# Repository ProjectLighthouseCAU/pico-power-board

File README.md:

# Schematic, PCB Layout and BOM for the new Power-and-Distribution Board
This PCB is meant to be used with the Raspberry Pi Pico with Ethernet e.g. Wiznet W5100S-EVB-Pico or W5500-EVB-Pico or optionally WiFi with the Pi Pico W.

## EDA Software and Manufacturer
The Design was made with KiCAD, a free and open-source program for electronic design automation (EDA).
It was chosen because a proprietary solution would be both very costly (or only available as a student) and also not free. Furthermore, we don't need the features that a commercial solution like Altium offers.
The PCBs will be manufactured and assembled at JLCPCB, a large chinese PCB manufacturing company based in Shenzhen that offers cheap services, good quality, fast assembly and shipping and also has a lot of parts ready in their own storage or source them directly from LCSC (big component distributor in China).

## Purpose and features of the PCB
The PCB acts as a kind of motherboard for the Pi Pico (+ e.g. W5100S or W5500) which can be mounted on top using two rows of 20 pin header sockets.
Further, it has a barrel jack for a 12V power supply and a step down converter from 12V to 3.3V to power the Pico and lamp microcontrollers.
The board features six 20-pin IDC connectors where Lighthouse lamps can be connected via flat cables.  
The connectors (and cables) contain an SPI bus (MISO, MOSI, SCK, CS), 3.3V, Reset, 12V (on six wires) and GND (on 8 wires).  
Additional fearures are:
- polyfuses for each lamp with a detection (via voltage divider) if the fuse has tripped
- current measurement IC (TI INA219) with a shunt resistor to monitor power draw
- thermal sensor (TI TMP112A) to monitor temperature
- I2C and UART breakout pins for testing, adding devices and hacking stuff together
- signal termination resistors for SPI data lines and RESET to reduce ringing and over-/undershoot (series termination for SCK, MOSI, CS and RESET, thevenin termination for MOSI)

## Design Decisions

### Microcontroller
The Raspberry Pi Pico together with the Wiznet W5500 (or W5100S) provides a performant, reliable and cheap alternative to other ethernet capable microcontrollers.  
The previously used Atmel/Microchip ATTiny841 with the ENC28J60 was too unreliable and had insufficient performance and memory.
Ethernet capable STM32 chips would be a good alternative but those that feature Ethernet support are too expensive and also require a complete board design (instead of the now chosen "motherboard" solution).
Teensy boards have great performance but are way too expensive. Same holds for Raspberry Pis and other single board computers.  
In fact, after a lot of research we found many wireless capable microcontrollers (e.g. the official Pi Pico W and ESP32) because of the increasing popularity of the Internet of Things (IoT) but finding good and cheap Ethernet capable MCUs was difficult.  
Therefore we were glad that Wiznet released their Pi Pico based boards.
The C/C++ Pico SDK is well documented and easy to work with and the Wiznet library is also okay and features the Berkeley socket API and some examples.
Nevertheless, we decided to rewrite the firmware in Rust for the Pi Pico with the W5500.

### Motherboard instead of complete "bare" chip design
We chose to design a simple motherboard for the finished Pi Pico board because it was easier and faster to design with less possibilities for mistakes (at least on the MCU side).  
We simply added a DC-Jack, six IDC connectors and a step-down-converter together with some sensors, fuses and connected everything accordingly.

### Fuses
We need fuses for each lamp because if we have one 10A fuse for all lamps and one lamp has a short circuit, then up to 10A may flow through that one lamp which is too much and could cause a fire.  
We measured the maximum current that a lamp can draw which is about 1.6A and selected a 2A fuse. The selected fuse is a polyfuse (or resettable fuse) which automatically resets itself (conducts again) after the current returns to a normal < 2A.  
We wanted to monitor if a fuse has tripped, so we took the 12V after the fuse, added a voltage divider to 3V and hooked that back up to the Pi Pico and also the reset line to that lamp.  
Therefore the lamp automatically resets (because reset is active low) and we don't need extra GPIOs on the Pico. If the Pico wants to manually reset a lamp, it just has to change the pin to output and pull it low. The current that then flows through the voltage divider and the GPIO is low enough for the maximum rating of the GPIO.

### Signal termination resistors

After looking at the SPI signal with an oscilloscope, we found out that the fast switching of voltage levels causes reflections on the end of the longer cables. These reflections interfere with each other constructively and cause ringing (voltage swings around the desired voltage at a rising/falling edge) and therefore over-/undershoot (voltage goes above/below the GPIO pins rated maximum/minimum voltage).  
While the SPI communication works and nothing broke yet, this over-/undervoltage could damage the GPIO pins or the whole microcontroller (both RP2040 and ATtiny841) in the long run.  
To fix this issue, we need to terminate the transmission line (cable) with properly sized terminating resistors with a suitable termination technique.  
Because we only change the hardware on one side of the transmission line, we need to choose the termination technique accordingly.  
There are three suitable termination techniques:
- Series termination (series resistor at the transmitter)
- Parallel termination (parallel resistor at the receiver, pull down to GND)
- Thevenin termination (voltage divider at the receiver)

#### Series termination for outgoing data lines
For the transmitting data lines (SCK, MOSI, CS, RESET), we chose series termination since it is the only termination that is recommended at the source. It also is the most widely used technique, gives good results and has no extra power usage. The only downside is that the resistor limits the current and therefore increases the rise-/fall-times of the signal (which is negligable in our case).

#### Thevenin termination for incoming data line
For the one incoming data line (MISO) we tried to use parallel termination but this technique has the downside that it draws a lot of current from the transmitter (ATtiny841) which it cannot provide. So the signal couldn't reach the required voltage for a logic 1.  
Alternatively we chose Thevenin termination, which uses a voltage divider at the receiving end to pull the line to a voltage between Vcc and GND. This makes it "easier" for the driver to pull the line high and low and solved the insufficient voltage issue. We chose to use resistors of equal size to pull the signal exaclty at the half of Vcc.

#### Terminating resistor value
The value for the terminating resistors was determined experimentally.
Ideally one would consult the datasheet of the cable for its characteristic impedance, but unfortunately no information about the installed cables was found.
So, we tried out several different resistor values and measured the maximum and minimum voltage, rise and fall time and visually inspected the ringing with an oscilloscope.
The results showed that a 100 Ohm resistor is suitable for series termination and two 200 Ohm resistors for Thevenin termination (since they are considered to be in parallel from the signals perspective, the combined resistance is 100 Ohm).
So the cables characteristic impedance is somewhere around 100 Ohm (+/- measurement inaccuracies and + ouput driver impedance).

#### Problem: SPI over long distance unshielded cable
We are aware that transmitting SPI signals over long unshielded cables can and will cause interference problems.  
The old system was designed like this to save on cost.
Adding transceivers for some kind of differential transmission on both ends and using shielded cables would be the ideal solution.  
But designing, buying and installing new transceiver boards for the lamps, new cables and connectors would be very time consuming and expensive.  
Since the old system worked well enough, we decided to try out a lower frequency, a line driver IC (which we found out was not needed), signal termination resistors and add some error detection (checksum/CRC).
Unfortunately, the return channel (MISO / lamp -> controller) had the most problems especially with longer transmissions of 8 bytes. This is partly caused by the unbuffered SPI data register of the ATtiny841. When the lamp doesn't update the data register in time, the controller reads (part of) the previous value. The only solution to fix this (after all optimizations) is to reduce the frequency.  

### Step-Down-Converter
We decided to use a drop-in replacement for a linear regulator since it provides a finished and tested solution for efficient voltage regulation and we don't need to calculate inductances and capacitances.
After all we are computer scientists and not electrical engineers and therefore will probably make mistakes.

Note that the original Pi Pico has a Step-Up/Step-Down converter builtin (with a maximum input of about 5V).
But the Wiznet W5100S-EVB-Pico has a linear regulator.
Because two Step-Downs can cause interference and a linear regulator is not well suited for "converting" 3.3V to 3.3V (it needs at least 1V higher input voltage), we opted to power the Pico using the 3V3(OUT)-pin instead of the VSYS-pin which connects to the point after its internal linear regulator.

### DC-Barrel-Jack
The barrel jack should support our 12V power supply connectors and be rated for 10A. It should also have an inner pin diameter of 2.5mm and an outer barrel diameter of 5.5mm (the outer diameter can be larger if it has a spring mechanism that holds the plug).

### Debug and extension header
We added a 6-pin header as a breakout for some GPIOs of the pico.
They can be used for debugging or manually extending some functionality.  
These are:  
- UART (TX+RX)
- I2C (SDA+SCL)
- 3.3V
- GND

### Mounting Holes
The mounting holes are spaced to fit our old plastic cases.
(84mmx55.5mm)

### Current Measurement
We chose the INA219 from Texas Instruments together with a 10mOhm current shunt resistor. The INA219 features a current sensing amplifier, a precision ADC and an I2C interface.
We can configure the chip with the shunt resistance and then query voltage-drop, input-voltage, current and power.

### Temperature Measurement
The Pico has a builtin temperature sensor but it is not very accurate and also inside of the chip where any heat from the CPU is measured as well. We therefore added a small temperature sensor from Texas Instruments (TMP112A) which also has an I2C interface. This temperature sensor is installed near the barrel jack to measure the temperature increase from the current flowing through the 12V trace.

### Bypass capacitors
The step-down-converter has a 100nF and a 10uF capacitor on the 12V side and a 22uF capacitor on the 3.3V side (all ceramic as mentioned in the datasheet).
The temperature sensor has a 10nF and the current sensor has a 100nF capacitor (as mentioned in the datasheet).
The header for the Pi Pico has a 100nF and a 22pF capacitor at the 3.3V input.

## Insecurities / TODOs / To-Checks

### Trace width
Especially 12V high current traces (to the lamps).

### Trace spacing and routing
- enough spacing between tracks?
- too many vias?
- signal trace routing okay?

### Current return paths through GND plane
Is the current return path through the GND plane large and direct enough?
The signal traces on the bottom side were routed back to the top for short distances to keep a clear path from the GND of the connectors to the GND of the barrel jack.

### Double-check components
- check datasheets, bypass capacitors
- check footprints
- check placement and rotation files
- check BOM

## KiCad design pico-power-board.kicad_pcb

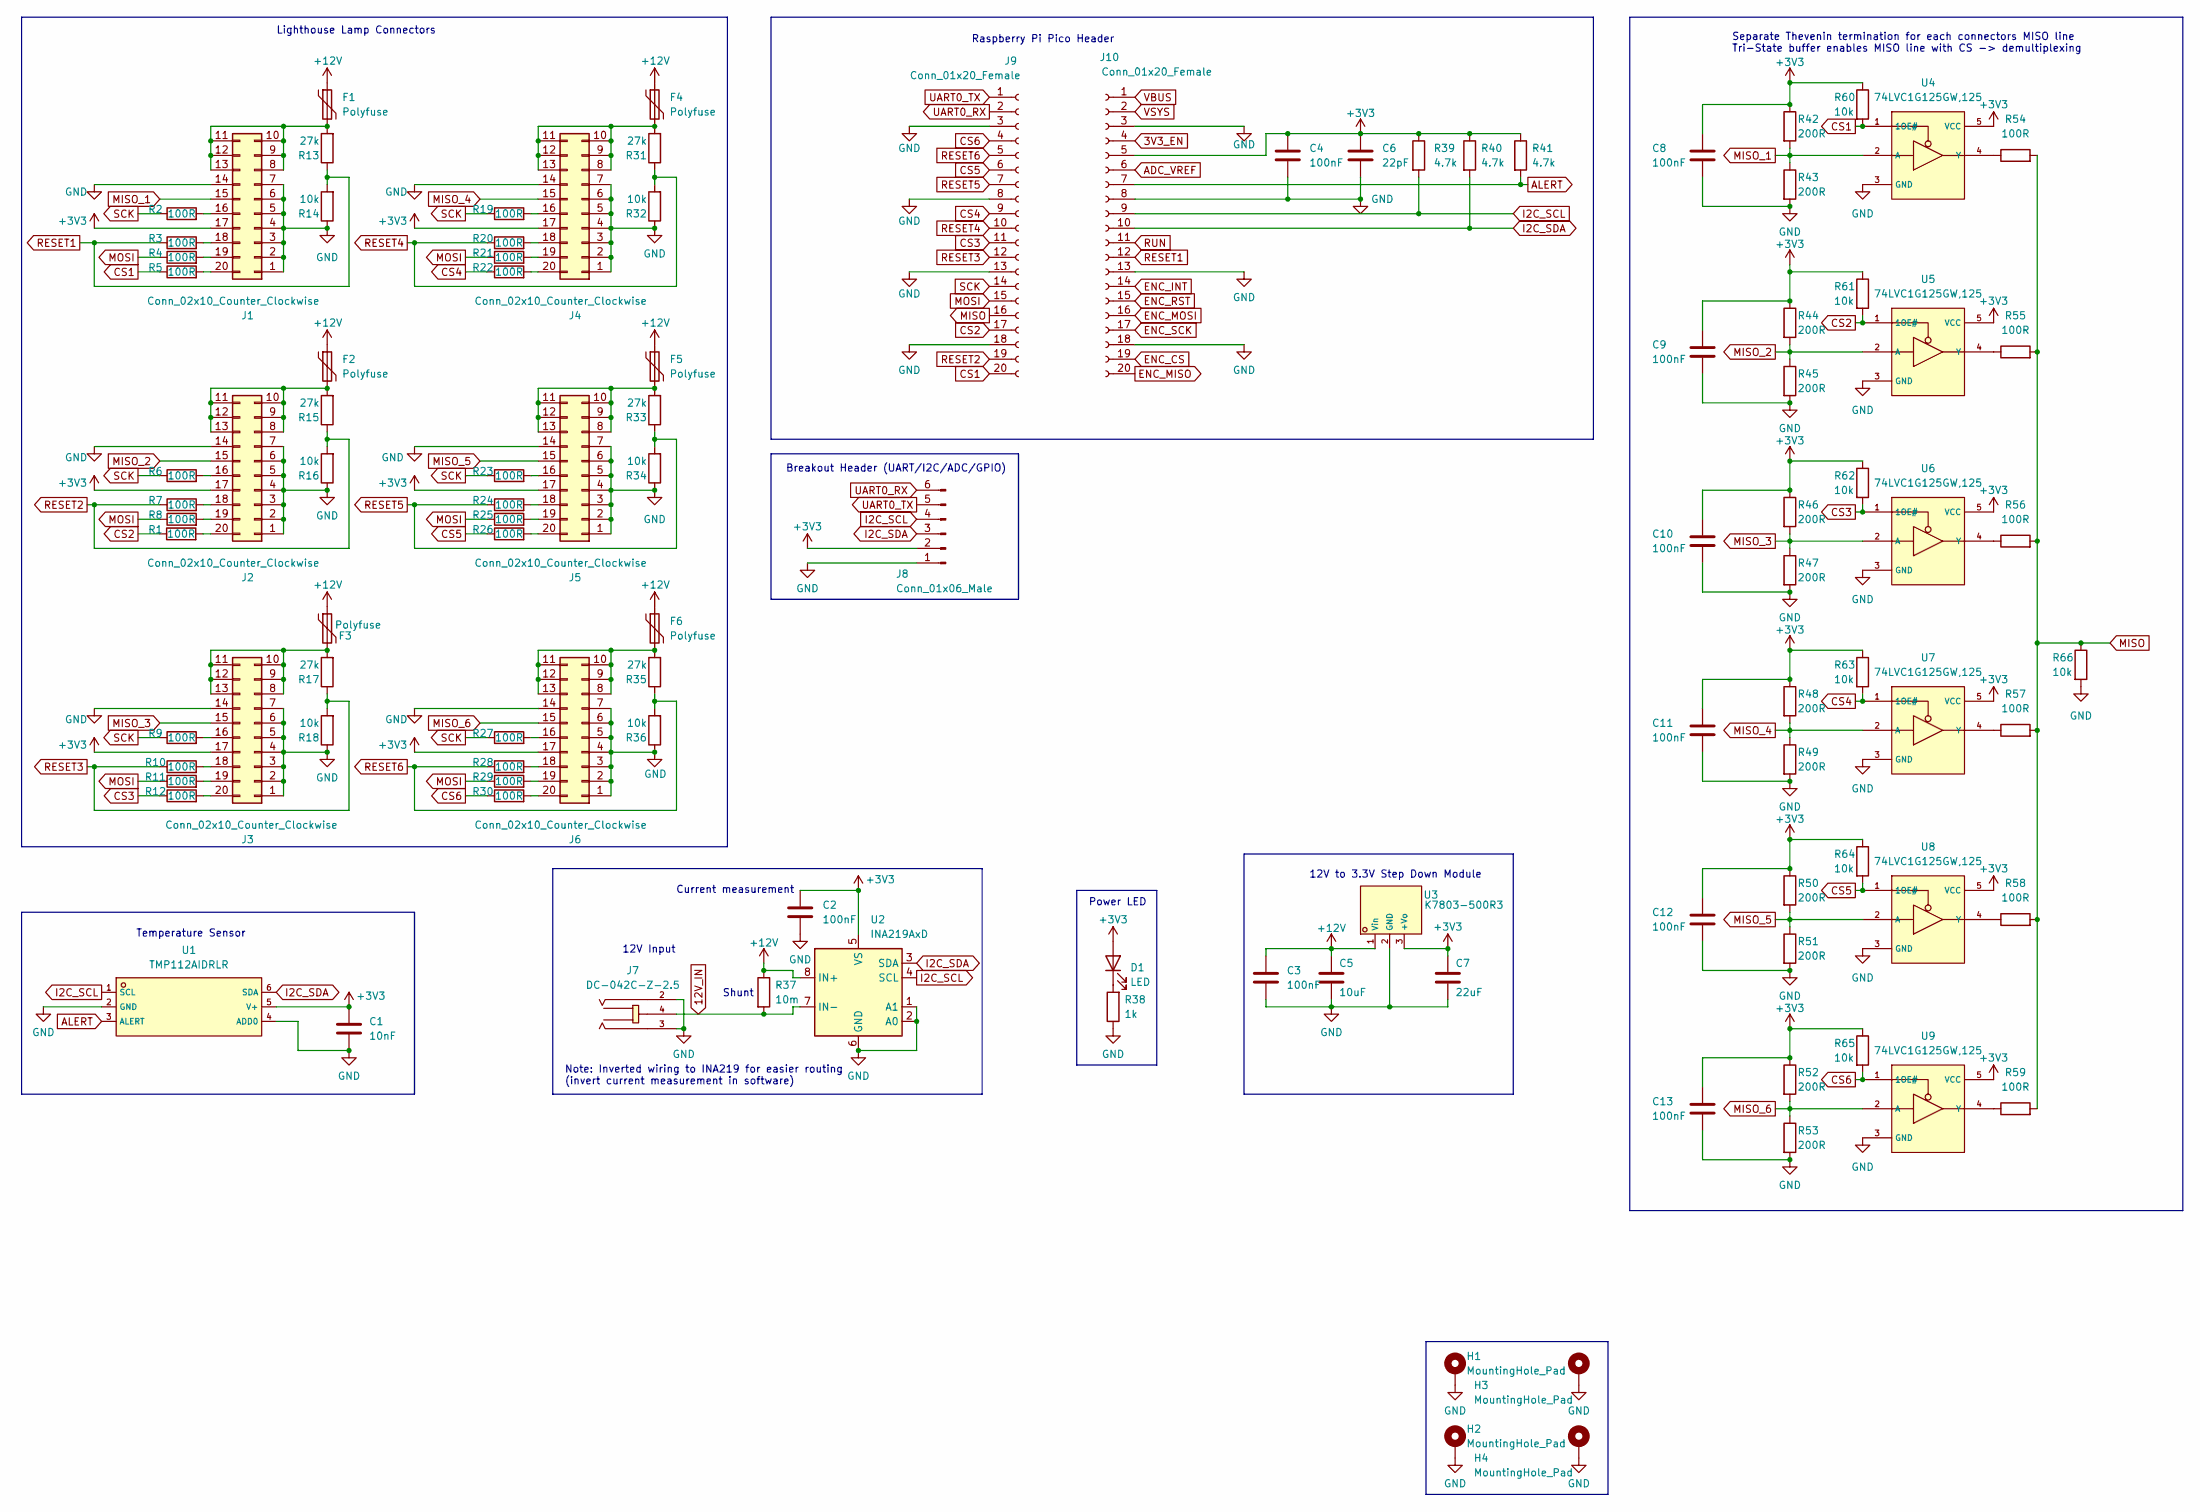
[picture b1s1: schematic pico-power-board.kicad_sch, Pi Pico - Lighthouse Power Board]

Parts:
C1: 10nF; C_0603_1608Metric; JLC 0603
C2, C3, C4, C8, C9, C10, C11, C12, C13: 100nF; C_0603_1608Metric; JLC 0603
C5: 10uF; C_1206_3216Metric; JLC 1206
C6: 22pF; C_0603_1608Metric; JLC 0603
C7: 22uF; C_0805_2012Metric; JLC 0805
D1: LED; LED_0603_1608Metric; JLC 0603
F1, F2, F3, F4, F5, F6: Polyfuse; Fuse_1206_3216Metric; JLC 1206
H1, H2, H3, H4: MountingHole_Pad; MountingHole_3.2mm_M3_DIN965_Pad
J1, J2, J3, J4, J5, J6: Conn_02x10_Counter_Clockwise; IDC-Header_2x10_P2.54mm_Vertical; JLC Plugin,P=2.54mm
J7: DC-042C-Z-2.5; DC-IN-TH_DC-042C-Z-2.5; LCSC C2880557
J8: Conn_01x06_Male; PinHeader_1x06_P2.54mm_Vertical; JLC Plugin,P=2.54mm
J9, J10: Conn_01x20_Female; PinSocket_1x20_P2.54mm_Vertical; JLC Plugin,P=2.54mm
R1, R2, R3, R4, R5, R6, R7, R8, R9, R10, R11, R12, R19, R20, R21, R22, R23, R24, R25, R26, R27, R28, R29, R30, R54, R55, R56, R57, R58, R59: 100R; R_0603_1608Metric; JLC 0603
R13, R15, R17, R31, R33, R35: 27k; R_0603_1608Metric; LCSC C308131
R14, R16, R18, R32, R34, R36: 10k; R_0603_1608Metric; LCSC C25804
R37: 10m; R_1206_3216Metric; JLC 1206
R38: 1k; R_0603_1608Metric; JLC 0603
R39, R40, R41: 4.7k; R_0603_1608Metric; JLC 0603
R42, R43, R44, R45, R46, R47, R48, R49, R50, R51, R52, R53: 200R; R_0603_1608Metric; JLC 0603
R60, R61, R62, R63, R64, R65, R66: 10k; R_0603_1608Metric; JLC 0603
U1: TMP112AIDRLR; SOT-563_L1.6-W1.2-P0.50-LS1.6-BR; LCSC C28927
U2: INA219AxD; SOIC-8_3.9x4.9mm_P1.27mm; JLC SOIC-8_150mil
U3: K7803-500R3; PWRM-TH_K7803-500R3; LCSC C86736
U4, U5, U6, U7, U8, U9: 74LVC1G125GW,125; SOT-353_L2.1-W1.3-P0.65-LS2.3-BR; LCSC C12519

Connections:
3V3_EN: J10.4
12V_IN: J7.4, R37.2, U2.7 (IN-)
+3V3: C1.1, C2.2, C4.1, C6.1, C7.1, C8.1, C9.1, C10.1, C11.1, C12.1, C13.1, D1.2 (A), J1.17, J2.17, J3.17, J4.17, J5.17, J6.17, J8.2, J10.5, R39.1, R40.1, R41.1, R42.1, R44.1, R46.1, R48.1, R50.1, R52.1, R60.1, R61.1, R62.1, R63.1, R64.1, R65.1, U1.5 (V+), U2.5 (VS), U3.3 (+Vo), U4.5 (VCC), U5.5 (VCC), U6.5 (VCC), U7.5 (VCC), U8.5 (VCC), U9.5 (VCC)
+12V: C3.1, C5.1, F1.1, F2.1, F3.1, F4.1, F5.1, F6.1, R37.1, U2.8 (IN+), U3.1 (Vin)
ADC_VREF: J10.6
ALERT: J10.7, R41.2, U1.3 (ALERT)
CS1: J9.20, R5.1, R60.2, U4.1 (1OE#)
CS2: J9.17, R1.1, R61.2, U5.1 (1OE#)
CS3: J9.11, R12.1, R62.2, U6.1 (1OE#)
CS4: J9.9, R22.1, R63.2, U7.1 (1OE#)
CS5: J9.6, R26.1, R64.2, U8.1 (1OE#)
CS6: J9.4, R30.1, R65.2, U9.1 (1OE#)
ENC_CS: J10.19
ENC_INT: J10.14
ENC_MISO: J10.20
ENC_MOSI: J10.16
ENC_RST: J10.15
ENC_SCK: J10.17
GND: C1.2, C2.1, C3.2, C4.2, C5.2, C6.2, C7.2, C8.2, C9.2, C10.2, C11.2, C12.2, C13.2, H1.1, H2.1, H3.1, H4.1, J1.1, J1.2, J1.3, J1.4, J1.5, J1.6, J1.7, J1.14, J2.1, J2.2, J2.3, J2.4, J2.5, J2.6, J2.7, J2.14, J3.1, J3.2, J3.3, J3.4, J3.5, J3.6, J3.7, J3.14, J4.1, J4.2, J4.3, J4.4, J4.5, J4.6, J4.7, J4.14, J5.1, J5.2, J5.3, J5.4, J5.5, J5.6, J5.7, J5.14, J6.1, J6.2, J6.3, J6.4, J6.5, J6.6, J6.7, J6.14, J7.2, J7.3, J8.1, J9.3, J9.8, J9.13, J9.18, J10.3, J10.8, J10.13, J10.18, R14.1, R16.1, R18.1, R32.1, R34.1, R36.1, R38.1, R43.2, R45.2, R47.2, R49.2, R51.2, R53.2, R66.2, U1.2 (GND), U1.4 (ADD0), U2.1 (A1), U2.2 (A0), U2.6 (GND), U3.2 (GND), U4.3 (GND), U5.3 (GND), U6.3 (GND), U7.3 (GND), U8.3 (GND), U9.3 (GND); also elsewhere on the board
I2C_SCL: J8.4, J10.9, R39.2, U1.1 (SCL), U2.4 (SCL)
I2C_SDA: J8.3, J10.10, R40.2, U1.6 (SDA), U2.3 (SDA)
MISO: J9.16, R54.2, R55.2, R56.2, R57.2, R58.2, R59.2, R66.1
MISO_1: J1.15, R42.2, R43.1, U4.2 (A)
MISO_2: J2.15, R44.2, R45.1, U5.2 (A)
MISO_3: J3.15, R46.2, R47.1, U6.2 (A)
MISO_4: J4.15, R48.2, R49.1, U7.2 (A)
MISO_5: J5.15, R50.2, R51.1, U8.2 (A)
MISO_6: J6.15, R52.2, R53.1, U9.2 (A)
MOSI: J9.15, R4.1, R8.1, R11.1, R21.1, R25.1, R29.1
unnamed: D1.1 (K), R38.2
unnamed: F1.2, J1.8, J1.9, J1.10, J1.11, J1.12, J1.13, R13.2
unnamed: J1.16, R2.2
unnamed: J1.18, R3.2
unnamed: J1.19, R4.2
unnamed: J1.20, R5.2
unnamed: F2.2, J2.8, J2.9, J2.10, J2.11, J2.12, J2.13, R15.2
unnamed: J2.16, R6.2
unnamed: J2.18, R7.2
unnamed: J2.19, R8.2
unnamed: J2.20, R1.2
unnamed: F3.2, J3.8, J3.9, J3.10, J3.11, J3.12, J3.13, R17.2
unnamed: J3.16, R9.2
unnamed: J3.18, R10.2
unnamed: J3.19, R11.2
unnamed: J3.20, R12.2
unnamed: F4.2, J4.8, J4.9, J4.10, J4.11, J4.12, J4.13, R31.2
unnamed: J4.16, R19.2
unnamed: J4.18, R20.2
unnamed: J4.19, R21.2
unnamed: J4.20, R22.2
unnamed: F5.2, J5.8, J5.9, J5.10, J5.11, J5.12, J5.13, R33.2
unnamed: J5.16, R23.2
unnamed: J5.18, R24.2
unnamed: J5.19, R25.2
unnamed: J5.20, R26.2
unnamed: F6.2, J6.8, J6.9, J6.10, J6.11, J6.12, J6.13, R35.2
unnamed: J6.16, R27.2
unnamed: J6.18, R28.2
unnamed: J6.19, R29.2
unnamed: J6.20, R30.2
unnamed: R54.1, U4.4 (Y)
unnamed: R55.1, U5.4 (Y)
unnamed: R56.1, U6.4 (Y)
unnamed: R57.1, U7.4 (Y)
unnamed: R58.1, U8.4 (Y)
unnamed: R59.1, U9.4 (Y)
RESET1: J10.12, R3.1, R13.1, R14.2
RESET2: J9.19, R7.1, R15.1, R16.2
RESET3: J9.12, R10.1, R17.1, R18.2
RESET4: J9.10, R20.1, R31.1, R32.2
RESET5: J9.7, R24.1, R33.1, R34.2
RESET6: J9.5, R28.1, R35.1, R36.2
RUN: J10.11
SCK: J9.14, R2.1, R6.1, R9.1, R19.1, R23.1, R27.1
UART0_RX: J8.6, J9.2
UART0_TX: J8.5, J9.1
VBUS: J10.1
VSYS: J10.2

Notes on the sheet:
12V to 3.3V Step Down Module
Temperature Sensor
Breakout Header (UART/I2C/ADC/GPIO)
Note: Inverted wiring to INA219 for easier routing (invert current measurement in software)
Current measurement
12V Input
Separate Thevenin termination for each connectors MISO line Tri-State buffer enables MISO line with CS -> demultiplexing
Shunt
Lighthouse Lamp Connectors
Power LED
Raspberry Pi Pico Header

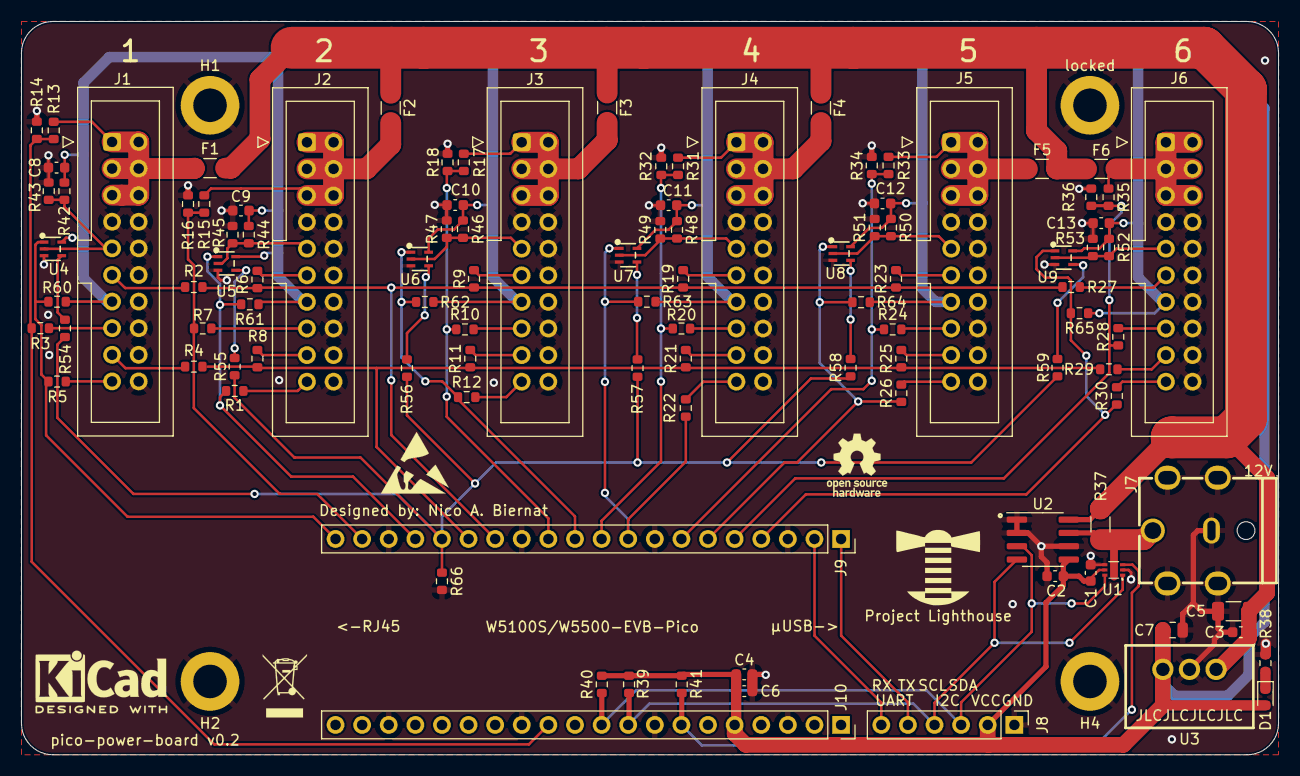
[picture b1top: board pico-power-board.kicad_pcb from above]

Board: 2 copper layers, 120.0 x 70.0 mm, 114 parts (0 on the bottom side), 67 nets.

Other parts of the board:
G_LH: LOGO; Lighthouse-Logo
REF_ESD: ESD-Logo_6.6x6mm_SilkScreen
REF_KiCad: KiCad-Logo2_5mm_SilkScreen
REF_OSH: OSHW-Logo_5.7x6mm_SilkScreen
REF_WEEE: WEEE-Logo_4.2x6mm_SilkScreen
locked: MountingHole_Pad; MountingHole_3.2mm_M3_DIN965_Pad

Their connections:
GND: locked.1; also elsewhere on the board

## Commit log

2022-12-29 Add design decisions and To-Check sections in README
2023-04-27 Update project for prototyping
2023-05-08 Implement improvements from review comments
2023-07-27 Progress, I guess
2023-07-27 Add SPI signal termination and remove line driver
2023-08-01 Refactor schematic and change temperature sensor from TMP102 to TMP112
2023-08-08 Change DC-Jack to an available option, add logos and some trace refactoring
2023-08-08 Create LICENSE
2023-08-13 Add tri-state buffers to each connectors MISO line in order to Thevenin-terminate them separately and add decoupling capacitors to the termination, change LED and series resistor, change I2C pull-ups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
2023-08-24 Revision v0.1
2023-10-03 Fix wrong resistor 100k -> 100R, add teardrops, larger resistor to dim power led
2023-11-06 Move pico down in order to not interfere with the case on the backside
